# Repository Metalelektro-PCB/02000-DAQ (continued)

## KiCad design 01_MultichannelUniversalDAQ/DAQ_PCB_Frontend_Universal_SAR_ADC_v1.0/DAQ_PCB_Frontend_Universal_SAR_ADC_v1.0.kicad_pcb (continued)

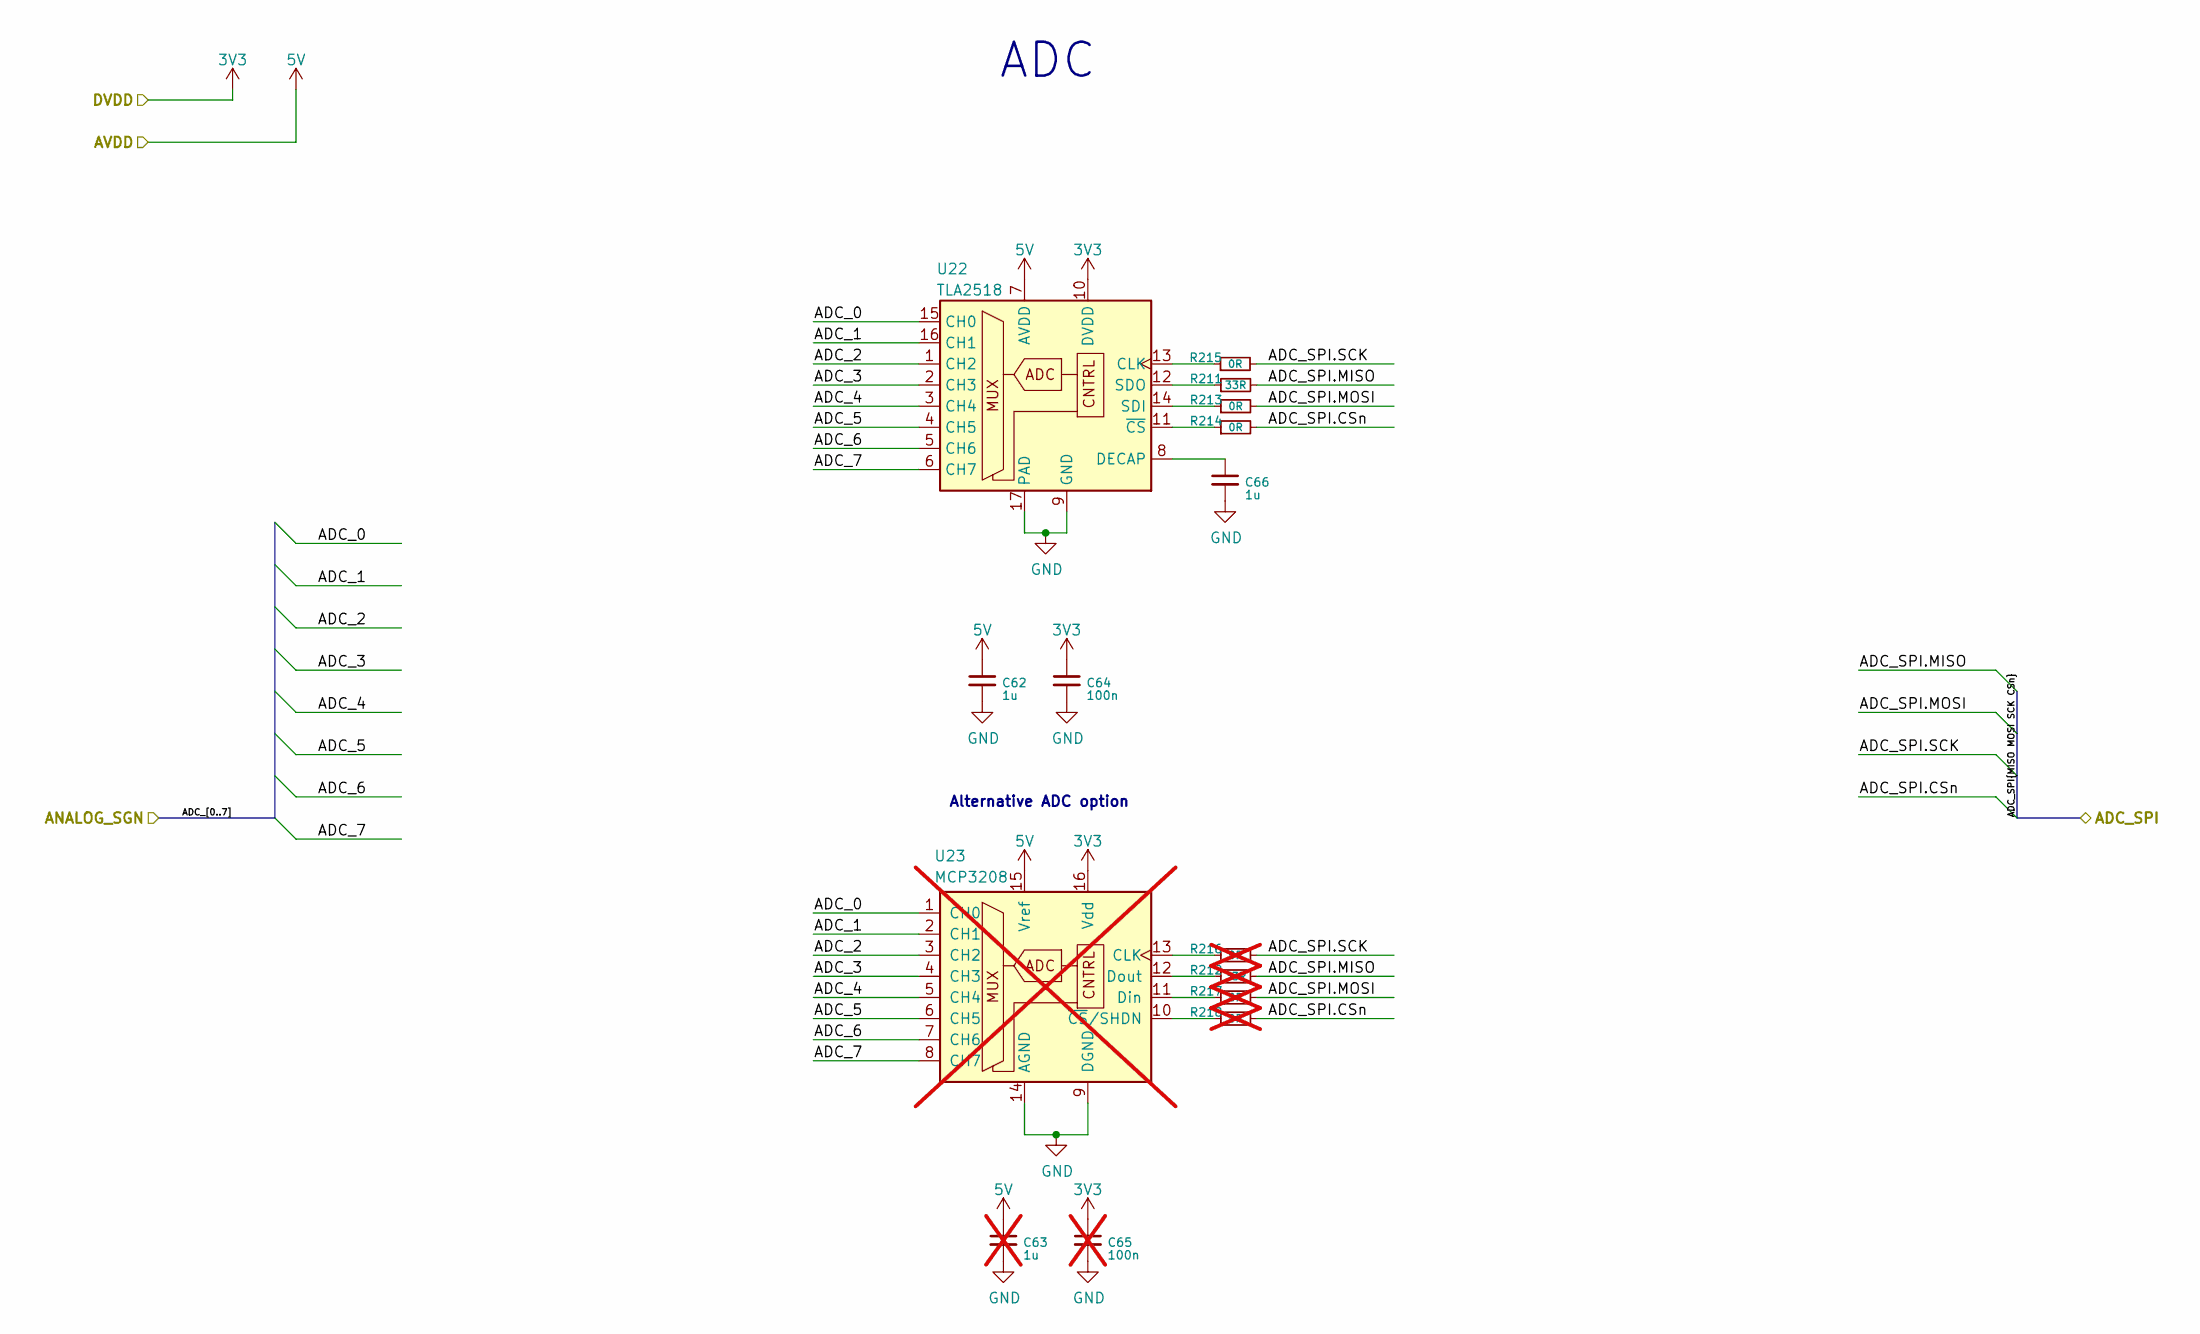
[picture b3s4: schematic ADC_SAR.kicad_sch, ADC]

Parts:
C62, C66: 1u; C_0603_1608Metric_Pad1.08x0.95mm_HandSolder
C63: 1u; C_0603_1608Metric_Pad1.08x0.95mm_HandSolder; not fitted
C64: 100n; C_0603_1608Metric_Pad1.08x0.95mm_HandSolder
C65: 100n; C_0603_1608Metric_Pad1.08x0.95mm_HandSolder; not fitted
R211: 33R; R_0603_1608Metric_Pad0.98x0.95mm_HandSolder
R212: 33R; R_0603_1608Metric_Pad0.98x0.95mm_HandSolder; not fitted
R213, R214, R215: 0R; R_0603_1608Metric_Pad0.98x0.95mm_HandSolder
R216, R217, R218: 0R; R_0603_1608Metric_Pad0.98x0.95mm_HandSolder; not fitted
U22: TLA2518; WQFN-16-1EP_3x3mm_P0.5mm_EP1.6x1.6mm; Part Number TLA2518IRTER
U23: MCP3208; SOIC-16_3.9x9.9mm_P1.27mm; not fitted

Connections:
3V3: C64.1, C65.1, U22.10 (DVDD), U23.16 (Vdd); also elsewhere on the board
5V: C62.1, C63.1, U22.7 (AVDD), U23.15 (Vref); also elsewhere on the board
/ADC/ADC_0: U22.15 (CH0), U23.1 (CH0); also elsewhere on the board
/ADC/ADC_1: U22.16 (CH1), U23.2 (CH1); also elsewhere on the board
/ADC/ADC_2: U22.1 (CH2), U23.3 (CH2); also elsewhere on the board
/ADC/ADC_3: U22.2 (CH3), U23.4 (CH3); also elsewhere on the board
/ADC/ADC_4: U22.3 (CH4), U23.5 (CH4); also elsewhere on the board
/ADC/ADC_5: U22.4 (CH5), U23.6 (CH5); also elsewhere on the board
/ADC/ADC_6: U22.5 (CH6), U23.7 (CH6); also elsewhere on the board
/ADC/ADC_7: U22.6 (CH7), U23.8 (CH7); also elsewhere on the board
/ADC/ADC_SPI.CSn: R214.2, R218.2; also elsewhere on the board
/ADC/ADC_SPI.MISO: R211.2, R212.2; also elsewhere on the board
/ADC/ADC_SPI.MOSI: R213.2, R217.2; also elsewhere on the board
/ADC/ADC_SPI.SCK: R215.2, R216.2; also elsewhere on the board
GND: C62.2, C63.2, C64.2, C65.2, C66.2, U22.9 (GND), U22.17 (PAD), U23.9 (DGND), U23.14 (AGND); also elsewhere on the board
unnamed: R215.1, U22.13 (CLK)
unnamed: C66.1, U22.8 (DECAP)
unnamed: R213.1, U22.14 (SDI)
unnamed: R211.1, U22.12 (SDO)
unnamed: R214.1, U22.11 (~CS)
unnamed: R216.1, U23.13 (CLK)
unnamed: R217.1, U23.11 (Din)
unnamed: R212.1, U23.12 (Dout)
unnamed: R218.1, U23.10 (~CS/SHDN)

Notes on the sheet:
Alternative ADC option
ADC

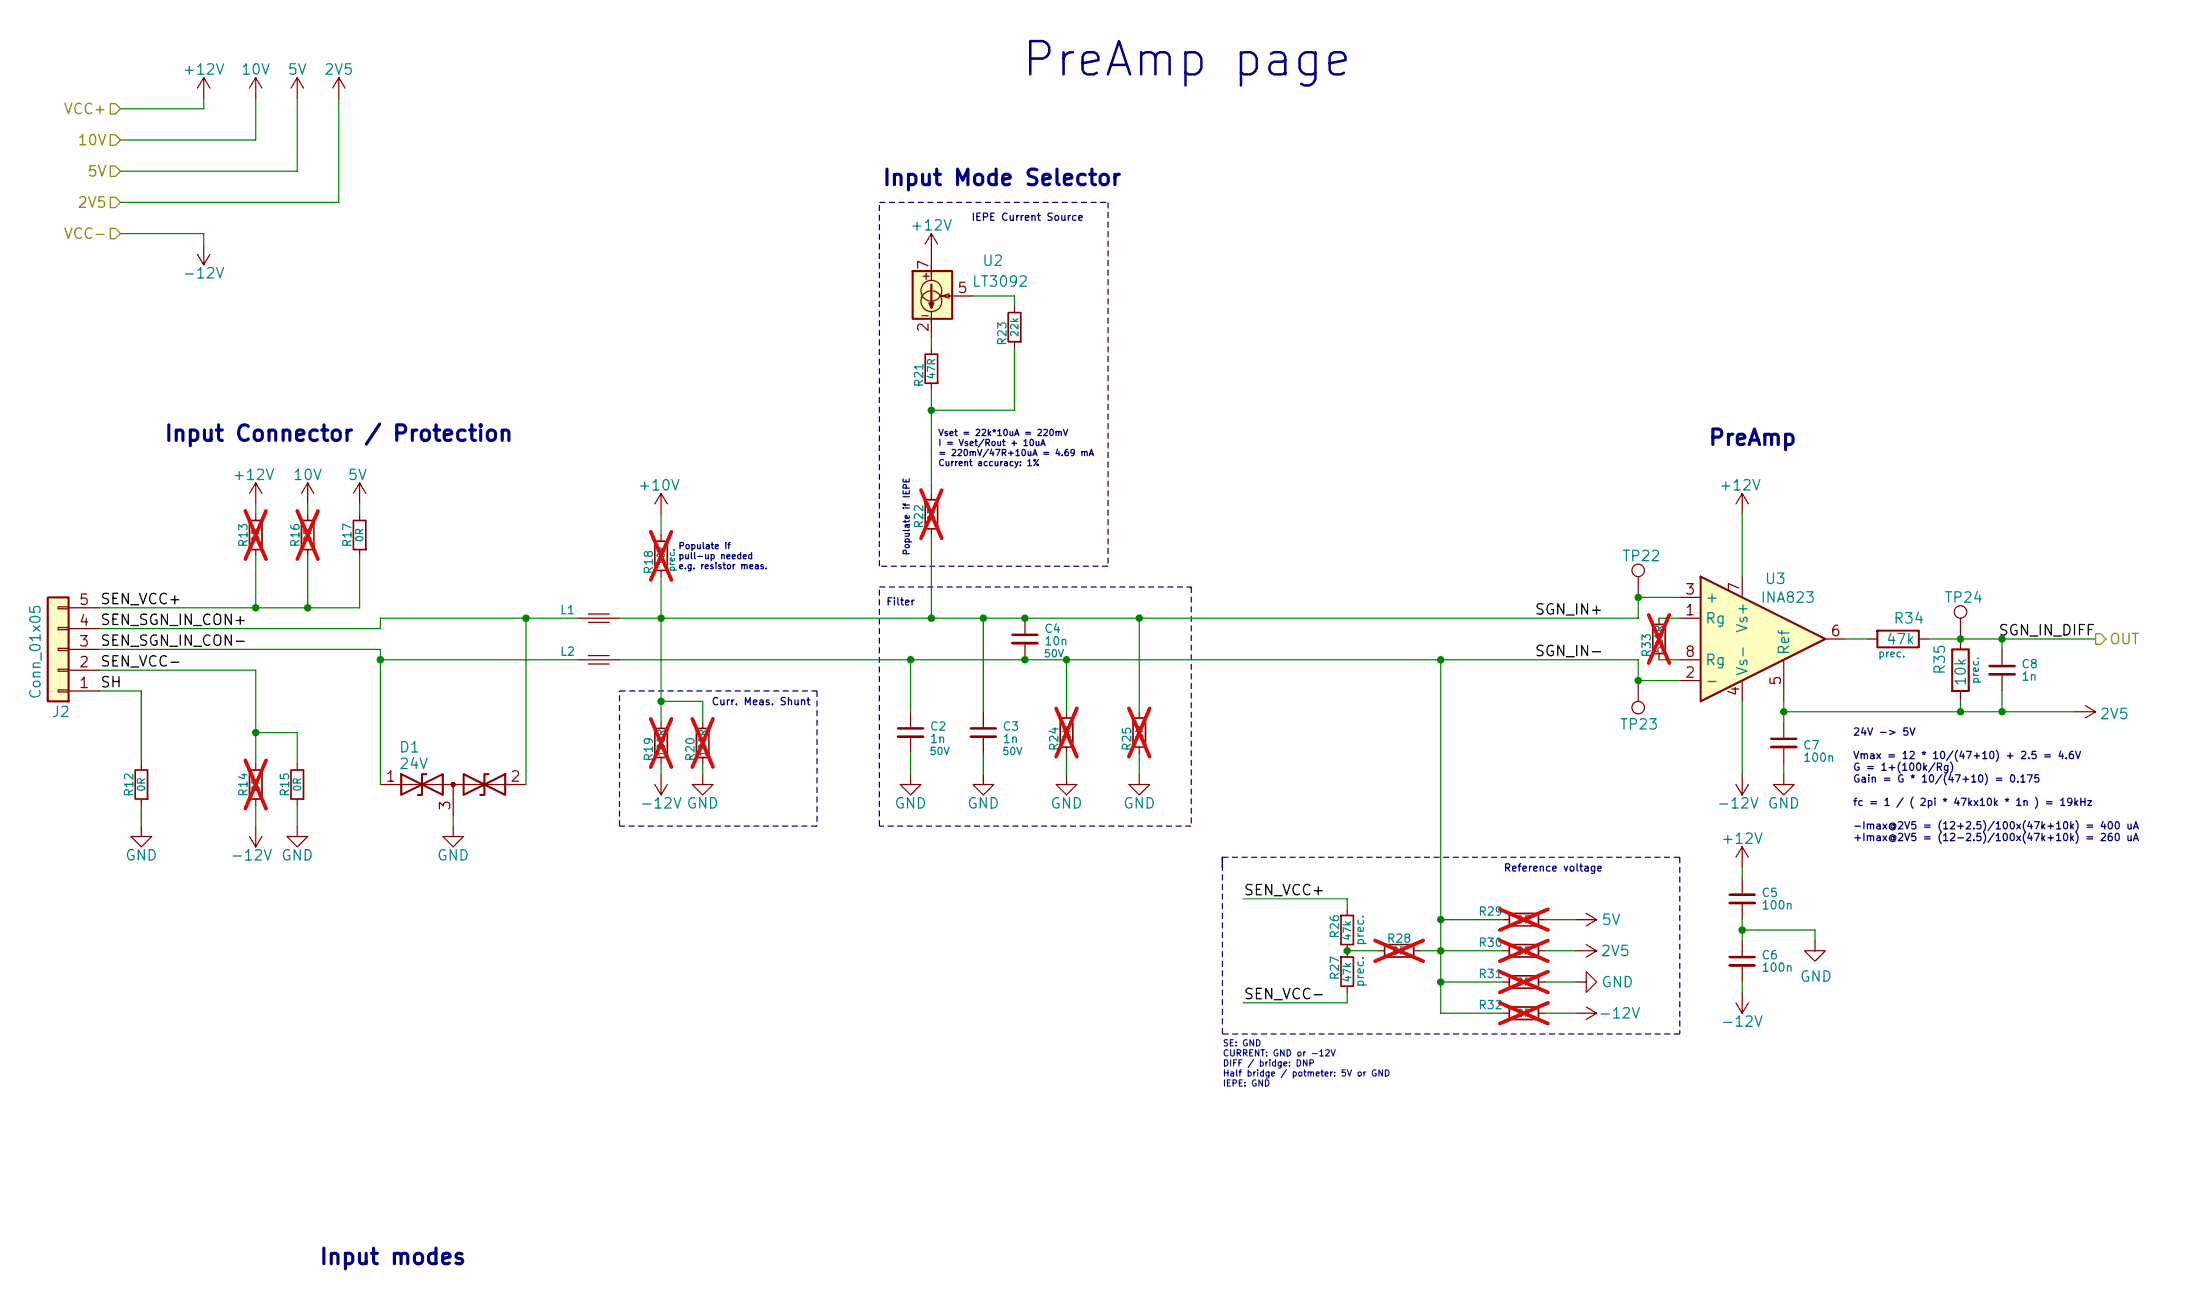
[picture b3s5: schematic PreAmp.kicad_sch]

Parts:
C2, C3: 1n; C_0603_1608Metric_Pad1.08x0.95mm_HandSolder; Voltage 50V
C4: 10n; C_0603_1608Metric_Pad1.08x0.95mm_HandSolder; Voltage 50V
C5, C6, C7: 100n; C_0603_1608Metric_Pad1.08x0.95mm_HandSolder
C8: 1n; C_0603_1608Metric_Pad1.08x0.95mm_HandSolder
D1: 24V; SOT-323_SC-70; Part Number VCAN33A2-03G-E3-08
J2: Conn_01x05; Molex_KK-254_AE-6410-05A_1x05_P2.54mm_Vertical
L1, L2: MPZ2012S601AT000; L_0805_2012Metric_Pad1.05x1.20mm_HandSolder; Part Number MPZ2012S601AT000
R12, R15, R17: 0R; R_0805_2012Metric_Pad1.20x1.40mm_HandSolder
R13, R14, R16, R22, R28, R29, R30, R31, R32: 0R; R_0805_2012Metric_Pad1.20x1.40mm_HandSolder; not fitted
R18: 10k; R_0805_2012Metric_Pad1.20x1.40mm_HandSolder; not fitted
R19, R20: 100R; R_0805_2012Metric_Pad1.20x1.40mm_HandSolder; not fitted
R21: 47R; R_0603_1608Metric_Pad0.98x0.95mm_HandSolder
R23: 22k; R_0603_1608Metric_Pad0.98x0.95mm_HandSolder
R24, R25: 1M; R_0805_2012Metric_Pad1.20x1.40mm_HandSolder; not fitted
R26, R27: 47k; R_0603_1608Metric_Pad0.98x0.95mm_HandSolder
R33: 510R; R_0805_2012Metric_Pad1.20x1.40mm_HandSolder; not fitted
R34: 47k; R_0603_1608Metric; Part Number RT0603DRD0733KL
R35: 10k; R_0603_1608Metric; Part Number RT0603DRD0733KL
TP22, TP23, TP24: TestPoint; TestPoint_Pad_D1.0mm
U2: LT3092; TSOT-23-8; Part Number LT3092ETS8#TRPBF
U3: INA823; SOIC-8_5.3x6.2mm_P1.27mm; Part Number INA823DR

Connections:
2V5: C7.1, C8.2, R30.2, R35.2, U3.5 (Ref); also elsewhere on the board
5V: R17.2, R29.2; also elsewhere on the board
10V: R16.2; also elsewhere on the board
+10V: R18.2; also elsewhere on the board
+12V: C5.1, R13.2, U2.7, U2.8, U3.7 (Vs+); also elsewhere on the board
-12V: C6.2, R14.1, R19.1, R32.2, U3.4 (Vs-); also elsewhere on the board
/Frontend/PREAMP2/SEN_SGN_IN_CON+: D1.2 (A2), J2.4, L1.1
/Frontend/PREAMP2/SEN_SGN_IN_CON-: D1.1 (A1), J2.3, L2.1
/Frontend/PREAMP2/SEN_VCC+: J2.5, R13.1, R16.1, R17.1, R26.1
/Frontend/PREAMP2/SEN_VCC-: J2.2, R14.2, R15.2, R27.2
/Frontend/PREAMP2/SGN_IN+: C3.1, C4.1, L1.2, R18.1, R19.2, R20.2, R22.2, R25.2, TP22.1 (1_1), U3.3 (+)
/Frontend/PREAMP2/SGN_IN-: C2.1, C4.2, L2.2, R24.2, R28.2, R29.1, R30.1, R31.1, R32.1, TP23.1 (1_1), U3.2 (-)
/Frontend/PREAMP2/SH: J2.1, R12.2
/Frontend/SGN_1: C8.1, R34.1, R35.1, TP24.1 (1_1); also elsewhere on the board
GND: C2.2, C3.2, C5.2, C6.1, C7.2, D1.3 (common), R12.1, R15.1, R20.1, R24.1, R25.1, R31.2; also elsewhere on the board
unnamed: R21.1, R22.1, R23.1
unnamed: R21.2, U2.2, U2.3, U2.4
unnamed: R23.2, U2.5
unnamed: R26.2, R27.1, R28.1
unnamed: R33.1, U3.8 (Rg)
unnamed: R33.2, U3.1 (Rg)
unnamed: R34.2, U3.6

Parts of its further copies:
C13, C14, C20, C21, C27, C28, C34, C35, C41, C42, C48, C49, C55, C56: 1n; C_0603_1608Metric_Pad1.08x0.95mm_HandSolder; Voltage 50V
C15, C22, C29, C36, C43, C50, C57: 10n; C_0603_1608Metric_Pad1.08x0.95mm_HandSolder; Voltage 50V
C16, C17, C18, C23, C24, C25, C30, C31, C32, C37, C38, C39, C44, C45, C46, C51, C52, C53, C58, C59, C60: 100n; C_0603_1608Metric_Pad1.08x0.95mm_HandSolder
C19, C26, C33, C40, C47, C54, C61: 1n; C_0603_1608Metric_Pad1.08x0.95mm_HandSolder
D2, D3, D4, D5, D6, D7, D8: 24V; SOT-323_SC-70; Part Number VCAN33A2-03G-E3-08
J3, J4, J5, J6, J7, J8, J9: Conn_01x05; Molex_KK-254_AE-6410-05A_1x05_P2.54mm_Vertical
L3, L4, L5, L6, L7, L8, L9, L10, L11, L12, L13, L14, L15, L16: MPZ2012S601AT000; L_0805_2012Metric_Pad1.05x1.20mm_HandSolder; Part Number MPZ2012S601AT000
R37, R40, R42, R62, R65, R67, R87, R90, R92, R112, R115, R117, R137, R140, R142, R162, R165, R167, R187, R190, R192: 0R; R_0805_2012Metric_Pad1.20x1.40mm_HandSolder
R38, R39, R41, R47, R53, R54, R55, R56, R57, R63, R64, R66, R72, R78, R79, R80, R81, R82, R88, R89, R91, R97, R103, R104, R105, R106, R107, R113, R114, R116, R122, R128, R129, R130, R131, R132, R138, R139, R141, R147, R153, R154, R155, R156, R157, R163, R164, R166, R172, R178, R179, R180, R181, R182, R188, R189, R191, R197, R203, R204, R205, R206, R207: 0R; R_0805_2012Metric_Pad1.20x1.40mm_HandSolder; not fitted
R43, R68, R93, R118, R143, R168, R193: 10k; R_0805_2012Metric_Pad1.20x1.40mm_HandSolder; not fitted
R44, R45, R69, R70, R94, R95, R119, R120, R144, R145, R169, R170, R194, R195: 100R; R_0805_2012Metric_Pad1.20x1.40mm_HandSolder; not fitted
R46, R71, R96, R121, R146, R171, R196: 47R; R_0603_1608Metric_Pad0.98x0.95mm_HandSolder
R48, R73, R98, R123, R148, R173, R198: 22k; R_0603_1608Metric_Pad0.98x0.95mm_HandSolder
R49, R50, R74, R75, R99, R100, R124, R125, R149, R150, R174, R175, R199, R200: 1M; R_0805_2012Metric_Pad1.20x1.40mm_HandSolder; not fitted
R51, R52, R76, R77, R101, R102, R126, R127, R151, R152, R176, R177, R201, R202: 47k; R_0603_1608Metric_Pad0.98x0.95mm_HandSolder
R58, R83, R108, R133, R158, R183, R208: 510R; R_0805_2012Metric_Pad1.20x1.40mm_HandSolder; not fitted
R59, R84, R109, R134, R159, R184, R209: 47k; R_0603_1608Metric; Part Number RT0603DRD0733KL
R60, R85, R110, R135, R160, R185, R210: 10k; R_0603_1608Metric; Part Number RT0603DRD0733KL
TP33, TP34, TP35, TP36, TP37, TP38, TP39, TP40, TP41, TP42, TP43, TP44, TP45, TP46, TP47, TP48, TP49, TP50, TP51, TP52, TP53: TestPoint; TestPoint_Pad_D1.0mm
U8, U10, U12, U14, U16, U18, U20: LT3092; TSOT-23-8; Part Number LT3092ETS8#TRPBF
U9, U11, U13, U15, U17, U19, U21: INA823; SOIC-8_5.3x6.2mm_P1.27mm; Part Number INA823DR

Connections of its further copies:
2V5: C18.1, C19.2, C25.1, C26.2, C32.1, C33.2, C39.1, C40.2, C46.1, C47.2, C53.1, C54.2, C60.1, C61.2, R55.2, R60.2, R80.2, R85.2, R105.2, R110.2, R130.2, R135.2, R155.2, R160.2, R180.2, R185.2, R205.2, R210.2, U9.5 (Ref), U11.5 (Ref), U13.5 (Ref), U15.5 (Ref), U17.5 (Ref), U19.5 (Ref), U21.5 (Ref); also elsewhere on the board
5V: R42.2, R54.2, R67.2, R79.2, R92.2, R104.2, R117.2, R129.2, R142.2, R154.2, R167.2, R179.2, R192.2, R204.2; also elsewhere on the board
10V: R41.2, R66.2, R91.2, R116.2, R141.2, R166.2, R191.2; also elsewhere on the board
+10V: R43.2, R68.2, R93.2, R118.2, R143.2, R168.2, R193.2; also elsewhere on the board
+12V: C16.1, C23.1, C30.1, C37.1, C44.1, C51.1, C58.1, R38.2, R63.2, R88.2, R113.2, R138.2, R163.2, R188.2, U8.7, U8.8, U9.7 (Vs+), U10.7, U10.8, U11.7 (Vs+), U12.7, U12.8, U13.7 (Vs+), U14.7, U14.8, U15.7 (Vs+), U16.7, U16.8, U17.7 (Vs+), U18.7, U18.8, U19.7 (Vs+), U20.7, U20.8, U21.7 (Vs+); also elsewhere on the board
-12V: C17.2, C24.2, C31.2, C38.2, C45.2, C52.2, C59.2, R39.1, R44.1, R57.2, R64.1, R69.1, R82.2, R89.1, R94.1, R107.2, R114.1, R119.1, R132.2, R139.1, R144.1, R157.2, R164.1, R169.1, R182.2, R189.1, R194.1, R207.2, U9.4 (Vs-), U11.4 (Vs-), U13.4 (Vs-), U15.4 (Vs-), U17.4 (Vs-), U19.4 (Vs-), U21.4 (Vs-); also elsewhere on the board
/Frontend/PREAMP1/SEN_SGN_IN_CON+: D2.2 (A2), J3.4, L3.1
/Frontend/PREAMP1/SEN_SGN_IN_CON-: D2.1 (A1), J3.3, L4.1
/Frontend/PREAMP1/SEN_VCC+: J3.5, R38.1, R41.1, R42.1, R51.1
/Frontend/PREAMP1/SEN_VCC-: J3.2, R39.2, R40.2, R52.2
/Frontend/PREAMP1/SGN_IN+: C14.1, C15.1, L3.2, R43.1, R44.2, R45.2, R47.2, R50.2, TP33.1 (1_1), U9.3 (+)
/Frontend/PREAMP1/SGN_IN-: C13.1, C15.2, L4.2, R49.2, R53.2, R54.1, R55.1, R56.1, R57.1, TP34.1 (1_1), U9.2 (-)
/Frontend/PREAMP1/SH: J3.1, R37.2
/Frontend/PREAMP3/SEN_SGN_IN_CON+: D3.2 (A2), J4.4, L5.1
/Frontend/PREAMP3/SEN_SGN_IN_CON-: D3.1 (A1), J4.3, L6.1
/Frontend/PREAMP3/SEN_VCC+: J4.5, R63.1, R66.1, R67.1, R76.1
/Frontend/PREAMP3/SEN_VCC-: J4.2, R64.2, R65.2, R77.2
/Frontend/PREAMP3/SGN_IN+: C21.1, C22.1, L5.2, R68.1, R69.2, R70.2, R72.2, R75.2, TP36.1 (1_1), U11.3 (+)
/Frontend/PREAMP3/SGN_IN-: C20.1, C22.2, L6.2, R74.2, R78.2, R79.1, R80.1, R81.1, R82.1, TP37.1 (1_1), U11.2 (-)
/Frontend/PREAMP3/SH: J4.1, R62.2
/Frontend/PREAMP4/SEN_SGN_IN_CON+: D4.2 (A2), J5.4, L7.1
/Frontend/PREAMP4/SEN_SGN_IN_CON-: D4.1 (A1), J5.3, L8.1
/Frontend/PREAMP4/SEN_VCC+: J5.5, R88.1, R91.1, R92.1, R101.1
/Frontend/PREAMP4/SEN_VCC-: J5.2, R89.2, R90.2, R102.2
/Frontend/PREAMP4/SGN_IN+: C28.1, C29.1, L7.2, R93.1, R94.2, R95.2, R97.2, R100.2, TP39.1 (1_1), U13.3 (+)
/Frontend/PREAMP4/SGN_IN-: C27.1, C29.2, L8.2, R99.2, R103.2, R104.1, R105.1, R106.1, R107.1, TP40.1 (1_1), U13.2 (-)
/Frontend/PREAMP4/SH: J5.1, R87.2
/Frontend/PREAMP5/SEN_SGN_IN_CON+: D5.2 (A2), J6.4, L9.1
/Frontend/PREAMP5/SEN_SGN_IN_CON-: D5.1 (A1), J6.3, L10.1
/Frontend/PREAMP5/SEN_VCC+: J6.5, R113.1, R116.1, R117.1, R126.1
/Frontend/PREAMP5/SEN_VCC-: J6.2, R114.2, R115.2, R127.2
/Frontend/PREAMP5/SGN_IN+: C35.1, C36.1, L9.2, R118.1, R119.2, R120.2, R122.2, R125.2, TP42.1 (1_1), U15.3 (+)
/Frontend/PREAMP5/SGN_IN-: C34.1, C36.2, L10.2, R124.2, R128.2, R129.1, R130.1, R131.1, R132.1, TP43.1 (1_1), U15.2 (-)
/Frontend/PREAMP5/SH: J6.1, R112.2
/Frontend/PREAMP6/SEN_SGN_IN_CON+: D6.2 (A2), J7.4, L11.1
/Frontend/PREAMP6/SEN_SGN_IN_CON-: D6.1 (A1), J7.3, L12.1
/Frontend/PREAMP6/SEN_VCC+: J7.5, R138.1, R141.1, R142.1, R151.1
/Frontend/PREAMP6/SEN_VCC-: J7.2, R139.2, R140.2, R152.2
/Frontend/PREAMP6/SGN_IN+: C42.1, C43.1, L11.2, R143.1, R144.2, R145.2, R147.2, R150.2, TP45.1 (1_1), U17.3 (+)
/Frontend/PREAMP6/SGN_IN-: C41.1, C43.2, L12.2, R149.2, R153.2, R154.1, R155.1, R156.1, R157.1, TP46.1 (1_1), U17.2 (-)
/Frontend/PREAMP6/SH: J7.1, R137.2
/Frontend/PREAMP7/SEN_SGN_IN_CON+: D7.2 (A2), J8.4, L13.1
/Frontend/PREAMP7/SEN_SGN_IN_CON-: D7.1 (A1), J8.3, L14.1
/Frontend/PREAMP7/SEN_VCC+: J8.5, R163.1, R166.1, R167.1, R176.1
/Frontend/PREAMP7/SEN_VCC-: J8.2, R164.2, R165.2, R177.2
/Frontend/PREAMP7/SGN_IN+: C49.1, C50.1, L13.2, R168.1, R169.2, R170.2, R172.2, R175.2, TP48.1 (1_1), U19.3 (+)
/Frontend/PREAMP7/SGN_IN-: C48.1, C50.2, L14.2, R174.2, R178.2, R179.1, R180.1, R181.1, R182.1, TP49.1 (1_1), U19.2 (-)
/Frontend/PREAMP7/SH: J8.1, R162.2
/Frontend/PREAMP8/SEN_SGN_IN_CON+: D8.2 (A2), J9.4, L15.1
/Frontend/PREAMP8/SEN_SGN_IN_CON-: D8.1 (A1), J9.3, L16.1
/Frontend/PREAMP8/SEN_VCC+: J9.5, R188.1, R191.1, R192.1, R201.1
/Frontend/PREAMP8/SEN_VCC-: J9.2, R189.2, R190.2, R202.2
/Frontend/PREAMP8/SGN_IN+: C56.1, C57.1, L15.2, R193.1, R194.2, R195.2, R197.2, R200.2, TP51.1 (1_1), U21.3 (+)
/Frontend/PREAMP8/SGN_IN-: C55.1, C57.2, L16.2, R199.2, R203.2, R204.1, R205.1, R206.1, R207.1, TP52.1 (1_1), U21.2 (-)
/Frontend/PREAMP8/SH: J9.1, R187.2
/Frontend/SGN_0: C19.1, R59.1, R60.1, TP35.1 (1_1); also elsewhere on the board
/Frontend/SGN_2: C26.1, R84.1, R85.1, TP38.1 (1_1); also elsewhere on the board
/Frontend/SGN_3: C33.1, R109.1, R110.1, TP41.1 (1_1); also elsewhere on the board
/Frontend/SGN_4: C40.1, R134.1, R135.1, TP44.1 (1_1); also elsewhere on the board
/Frontend/SGN_5: C47.1, R159.1, R160.1, TP47.1 (1_1); also elsewhere on the board
/Frontend/SGN_6: C54.1, R184.1, R185.1, TP50.1 (1_1); also elsewhere on the board
/Frontend/SGN_7: C61.1, R209.1, R210.1, TP53.1 (1_1); also elsewhere on the board
GND: C13.2, C14.2, C16.2, C17.1, C18.2, C20.2, C21.2, C23.2, C24.1, C25.2, C27.2, C28.2, C30.2, C31.1, C32.2, C34.2, C35.2, C37.2, C38.1, C39.2, C41.2, C42.2, C44.2, C45.1, C46.2, C48.2, C49.2, C51.2, C52.1, C53.2, C55.2, C56.2, C58.2, C59.1, C60.2, D2.3 (common), D3.3 (common), D4.3 (common), D5.3 (common), D6.3 (common), D7.3 (common), D8.3 (common), R37.1, R40.1, R45.1, R49.1, R50.1, R56.2, R62.1, R65.1, R70.1, R74.1, R75.1, R81.2, R87.1, R90.1, R95.1, R99.1, R100.1, R106.2, R112.1, R115.1, R120.1, R124.1, R125.1, R131.2, R137.1, R140.1, R145.1, R149.1, R150.1, R156.2, R162.1, R165.1, R170.1, R174.1, R175.1, R181.2, R187.1, R190.1, R195.1, R199.1, R200.1, R206.2; also elsewhere on the board
unnamed: R46.1, R47.1, R48.1
unnamed: R46.2, U8.2, U8.3, U8.4
unnamed: R48.2, U8.5
unnamed: R51.2, R52.1, R53.1
unnamed: R58.1, U9.8 (Rg)
unnamed: R58.2, U9.1 (Rg)
unnamed: R59.2, U9.6
unnamed: R71.1, R72.1, R73.1
unnamed: R71.2, U10.2, U10.3, U10.4
unnamed: R73.2, U10.5
unnamed: R76.2, R77.1, R78.1
unnamed: R83.1, U11.8 (Rg)
unnamed: R83.2, U11.1 (Rg)
unnamed: R84.2, U11.6
unnamed: R96.1, R97.1, R98.1
unnamed: R96.2, U12.2, U12.3, U12.4
unnamed: R98.2, U12.5
unnamed: R101.2, R102.1, R103.1
unnamed: R108.1, U13.8 (Rg)
unnamed: R108.2, U13.1 (Rg)
unnamed: R109.2, U13.6
unnamed: R121.1, R122.1, R123.1
unnamed: R121.2, U14.2, U14.3, U14.4
unnamed: R123.2, U14.5
unnamed: R126.2, R127.1, R128.1
unnamed: R133.1, U15.8 (Rg)
unnamed: R133.2, U15.1 (Rg)
unnamed: R134.2, U15.6
unnamed: R146.1, R147.1, R148.1
unnamed: R146.2, U16.2, U16.3, U16.4
unnamed: R148.2, U16.5
unnamed: R151.2, R152.1, R153.1
unnamed: R158.1, U17.8 (Rg)
unnamed: R158.2, U17.1 (Rg)
unnamed: R159.2, U17.6
unnamed: R171.1, R172.1, R173.1
unnamed: R171.2, U18.2, U18.3, U18.4
unnamed: R173.2, U18.5
unnamed: R176.2, R177.1, R178.1
unnamed: R183.1, U19.8 (Rg)
unnamed: R183.2, U19.1 (Rg)
unnamed: R184.2, U19.6
unnamed: R196.1, R197.1, R198.1
unnamed: R196.2, U20.2, U20.3, U20.4
unnamed: R198.2, U20.5
unnamed: R201.2, R202.1, R203.1
unnamed: R208.1, U21.8 (Rg)
unnamed: R208.2, U21.1 (Rg)
unnamed: R209.2, U21.6

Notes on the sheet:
Input Connector / Protection
IEPE Current Source
Vset = 22k*10uA = 220mV I = Vset/Rout + 10uA = 220mV/47R+10uA = 4.69 mA Current accuracy: 1%
PreAmp page
SE: GND CURRENT: GND or -12V DIFF / bridge: DNP Half bridge / potmeter: 5V or GND IEPE: GND
Populate if pull-up needed e.g. resistor meas.
Input Mode Selector
24V -> 5V Vmax = 12 * 10/(47+10) + 2.5 = 4.6V G = 1+(100k/Rg) Gain = G * 10/(47+10) = 0.175 fc = 1 / ( 2pi * 47kx10k * 1n ) = 19kHz -Imax@2V5 = (12+2.5)/100x(47k+10k) = 400 uA +Imax@2V5 = (12-2.5)/100x(47k+10k) = 260 uA
Populate if IEPE
Reference voltage
Input modes
PreAmp
Filter
Curr. Meas. Shunt

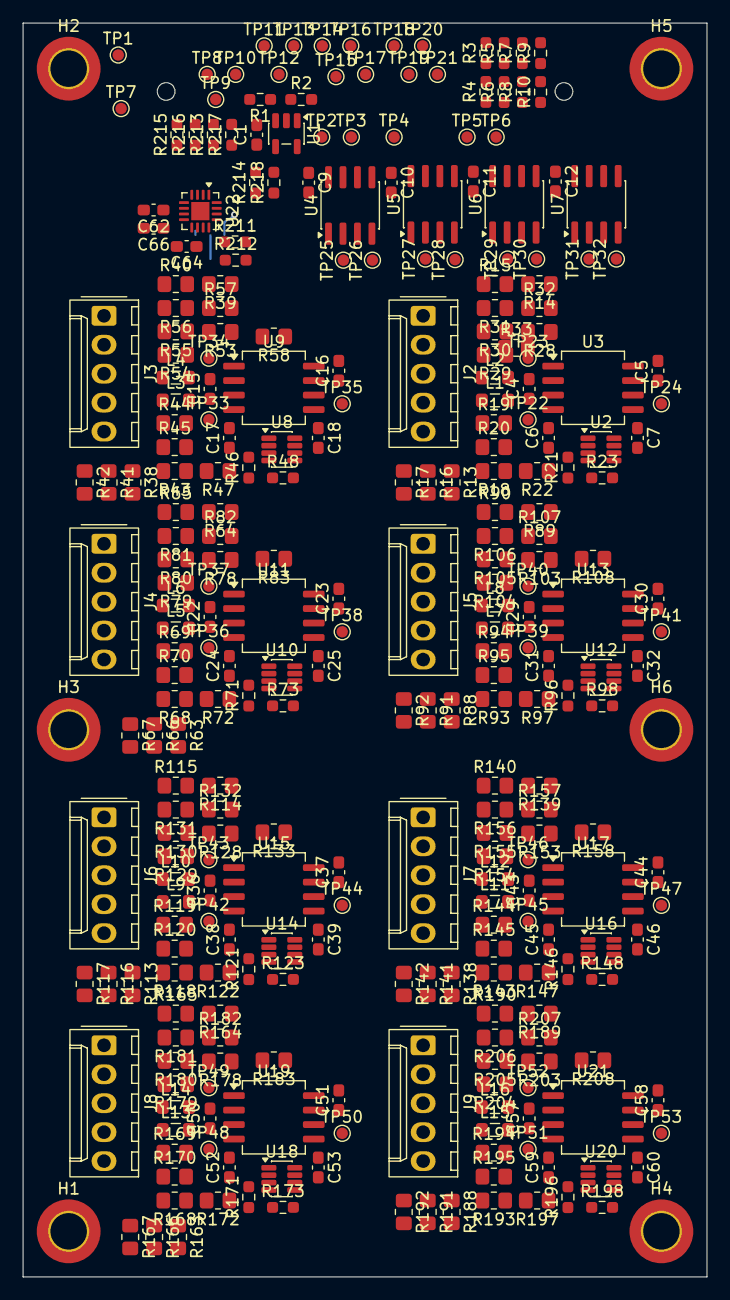
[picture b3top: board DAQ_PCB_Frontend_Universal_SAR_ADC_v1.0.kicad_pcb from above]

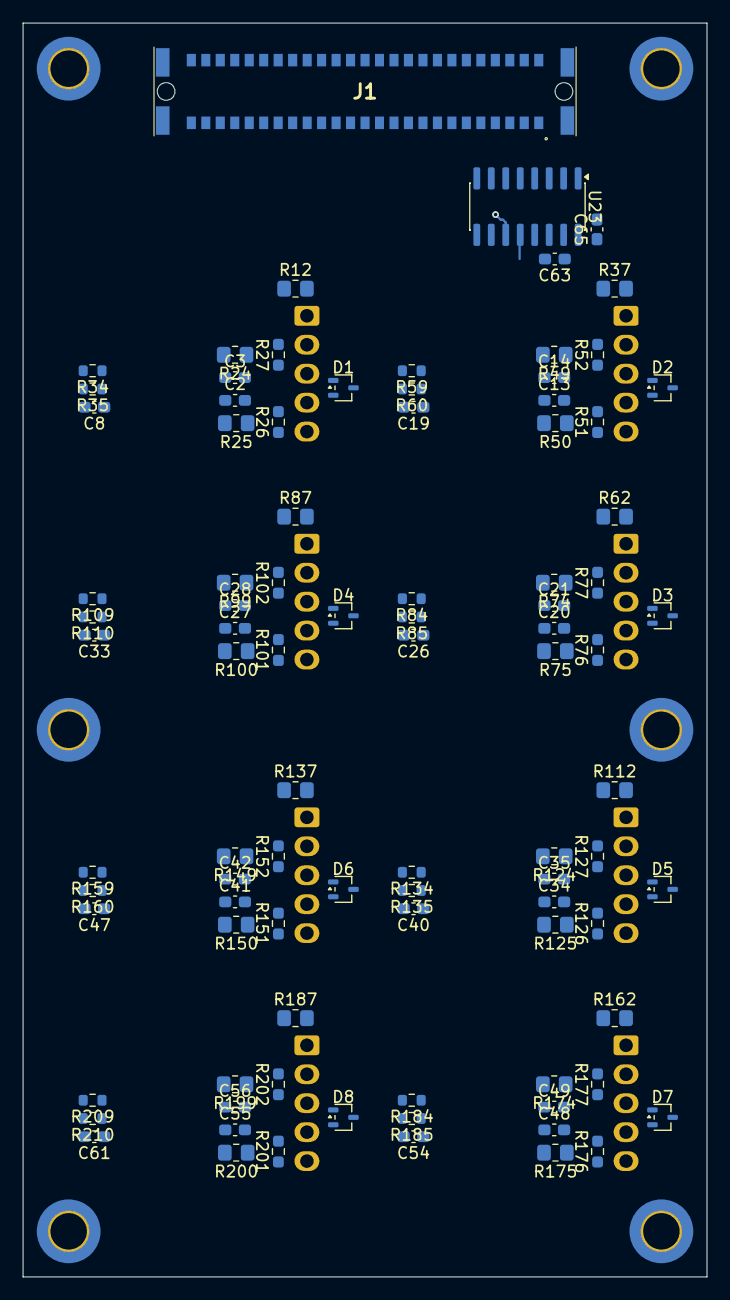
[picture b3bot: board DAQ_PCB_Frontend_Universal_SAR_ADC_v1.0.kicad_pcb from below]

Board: 2 copper layers, 60.0 x 110.0 mm, 391 parts (92 on the bottom side), 163 nets.

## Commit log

2026-04-22 bugfix
2026-04-22 0. placement concept (SAR_ADC)
2026-04-22 0. placement concept (RS485)
2026-04-28 Commit after meeting
2026-04-28 New power concept begin
2026-04-29 power in progress
2026-04-29 ADC és preamp in progress
2026-04-29 new power concept
2026-04-29 Power meas
2026-04-29 RefBuffer
